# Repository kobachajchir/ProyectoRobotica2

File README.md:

> **Loader AFR2-20261028-05 / 0.9.0:** backup opcional leído del ATmega, aviso con No mostrar de nuevo y Preferencias; botón Flashear Firmware ATmega con menú Flashear último backup. [Ficha](AutoFinalRobo2-Contracts/changes/2026-10-28-05-loader-mega-backups.md) · [Plan de ambos métodos](AutoFinalRobo2-Contracts/hardware/PLAN_PRUEBA_FLASHER_MEGA.md). Fuente/documentación, sin compilar, ejecutar, validar, abrir COM ni flashear; atmega/esp/web sin nuevo firmware por05. Los avisos de versiones inferiores son históricos.

> **Loader AFR2-20261028-03 / 0.8.0:** selector **Método ESP** con instrucciones/casillas, instalar flasher en Mega y restaurar producto. [Plan A/B](AutoFinalRobo2-Contracts/hardware/PLAN_PRUEBA_FLASHER_MEGA.md), [ficha](AutoFinalRobo2-Contracts/changes/2026-10-28-03-loader-mega-flasher.md). Implementado en fuente; sin compilar, ejecutar, validar, abrir COM ni flashear en esta entrega.

> **Loader AFR2-20261027-19 / 0.3.0:** [monitor serie y errores](AutoFinalRobo2-Loader/MANUAL.html#monitor), selección de baudios, COM abrir/cerrar, captura de texto/bytes y avisos de reinicio, programación y verificación. [Ficha](AutoFinalRobo2-Contracts/changes/2026-10-27-19-loader-serial-monitor.md). Fuente/documentación; sin compilar/ejecutar/probar ni abrir COM/flashear.

> **Loader AFR2-20261027-16 / 0.2.0:** [MCP para conectar con Codex](AutoFinalRobo2-Loader/MCP.md), revisión de solicitudes en GUI, historial y refuerzos de interfaz. [Ficha](AutoFinalRobo2-Contracts/changes/2026-10-27-16-loader-mcp-ui.md). Fuente/documentación; sin compilar, ejecutar, registrar MCP, probar COM ni flashear en esta revisión.

> **Vigente AFR2-20261025-01:** [control directo7](AutoFinalRobo2-Contracts/contracts/DIRECT_CONTROL_7.md), sin permiso ni opciones de adquisición. Los tres módulos compilan con firmware0.9.0/Web0.2.0. Estado anterior inferior histórico.

> **Vigente AFR2-20261024-15:** [Matriz del maestro](AutoFinalRobo2-Contracts/docs/ALINEACION_MAESTRO.md):33comandos y59identidades OLED con fuentes complementarias. Calibración Web adquiere control al escribir; ESP/Web informan FS/paquete. Web/ESP compilados15; AVR sin nueva fuente, build12/EX01v6/firmware0.8.0/gates0. Sin brecha software definida identificada tras lectura; aceptación física, memoria dinámica, flash/SPI y planos CAD pendientes. Solo documentación en CAD, sin diseño nuevo. Estados inferiores históricos.

> **Fuente vigente AFR2-20261024-11:** encoder CLK/DT en D2/D3 por INT4/INT5, SW D42; cola y acciones en main. Hall PCINT2 A8–A15 con preferencia de captura por software, macro0. **Esta adaptación no está compilada ni probada**; build08 corresponde a la fuente anterior. ESP/Web conservan su estado10. [Ficha11](AutoFinalRobo2-Contracts/changes/2026-10-24-11-encoder-hall-interrupts.md). Los estados previos inferiores son históricos.

> Vigente **AFR2-20261024-04**: **modelo final incluido en ESP**, paquete **1.450.201 bytes gzip** (49,96% menos que los 2,90 MB iniciales). WebP, JS/CSS minificados y dependencias/componentes optimizados. Layout candidato: flash 4 MiB / LittleFS nominal 3 MiB, solicitado por el usuario; flash fisica sin identificar. Web full/esp y firmware ESP compilados; activos promovidos a data/dist. Sin navegador, imagen FS ni flasheo. Atmega y comandos conservan el estado de02. [Evidencia](AutoFinalRobo2-Contracts/changes/2026-10-24-04-final-model-littlefs.md). Los estados previos inferiores son historicos.

> Estado vigente **AFR2-20261024-02**, 24/10/2026: integración ROBO2/perfil2 + EX01v3 compilada en Atmega/ESP/Web; GOTO completo, configuración por catálogo compartido y jobs Wi-Fi OLED conectados. Paquete Web actualizado en ESP/data/dist. Sin pruebas de navegador/hardware ni flasheo; secuencias físicas mantienen bloqueo de memoria. Ver [matriz vigente](AutoFinalRobo2-Contracts/contracts/EX01_ALIGNMENT_3.md) y [evidencia](AutoFinalRobo2-Contracts/changes/2026-10-24-02-project-alignment.md). Los estados previos que siguen son históricos.

# AutoFinalRobo2

Un único repositorio Git local en D:/ProyectoRobotica2, organizado en seis módulos. [Informe maestro](INFORME_MAESTRO.md) · [Central documental](AutoFinalRobo2-Contracts/README.md) · [Git, exclusiones e historial](AutoFinalRobo2-Contracts/docs/ESTRUCTURA_Y_GIT.md).

| Módulo | Contenido |
| --- | --- |
| [Atmega](AutoFinalRobo2-Atmega/README.md) | C/avr-libc para ATmega2560; fuente parcial con endpoint/USART1 |
| [ESP](AutoFinalRobo2-ESP/README.md) | Arduino ESP8266/LittleFS; servidor y broker escritos, sin compilar |
| [Web](AutoFinalRobo2-Web/README.md) | React/Vite; paquete previo y cambios fuente pendientes de reconstruir |
| [Contracts](AutoFinalRobo2-Contracts/README.md) | Contratos, hardware, evidencia y cambios AFR2 |
| [CAD](AutoFinalRobo2-CAD/README.md) | KiCad, pieza nueva y modelo completo del auto; estructura e insumos |
| [Loader](AutoFinalRobo2-Loader/README.md) | Cargador Windows: compilación y flasheo guiados de ATmega/ESP/Web/LittleFS; fuente sin ejecutar ni probar |

El trabajo de diseño eléctrico y mecánico se concentra en AutoFinalRobo2-CAD. Los insumos que estaban en CADS se conservan allí con inventario; Documentacion/ conserva los documentos originales. No iniciar un Git dentro de cada módulo.

El .gitignore global excluye dependencias instaladas, cachés, compilados y exportaciones regenerables. Se conservan fuentes editables, manifests, lockfiles, bibliotecas propias e insumos únicos. Origin privado: [kobachajchir/ProyectoRobotica2](https://github.com/kobachajchir/ProyectoRobotica2), rama remota main. Los cuatro historiales anteriores y sus etiquetas están conservados en el Git global.

Leer AGENTS.md antes de trabajar. No ejecutar tests, compilaciones, validadores, ERC/DRC, flasheos ni pruebas físicas sin pedido expreso. El plan 3D distingue el ensamble base con inferencias documentadas de la pieza nueva/PCB pendientes de planos; aún no hay un modelo adaptado.

Registro: [AFR2-20261023-04](AutoFinalRobo2-Contracts/changes/2026-10-23-04-cad-and-monorepo.md).

## Plan 3D y continuación

[Plan completo de Fusion](AutoFinalRobo2-CAD/docs/PLAN_MODELO_3D_FUSION.md): ensamble del auto base sin cables, fuentes CAD y pendientes de la pieza nueva. MCP de Fusion existente. OLED 0,96 pulgadas y encoder KY-040 sin breakout/perilla como referencias para la integración futura. Registro [AFR2-20261023-05](AutoFinalRobo2-Contracts/changes/2026-10-23-05-fusion-plan-and-origin.md).

Para bajar el proyecto en la otra PC, con acceso a tu cuenta de GitHub:

```powershell
git clone https://github.com/kobachajchir/ProyectoRobotica2.git
```

Abrir la carpeta clonada y empezar por AutoFinalRobo2-CAD/docs/PLAN_MODELO_3D_FUSION.md. El clone usa main; los resguardos locales dentro de .git no se transfieren, pero los commits históricos y sus etiquetas sí.

## Firmware ESP y comunicación — AFR2-20261023-11

[Estado de implementación y pendientes](AutoFinalRobo2-Contracts/changes/2026-10-23-11-esp-server-and-mega-link.md): HTTP/WS/LittleFS/Wi-Fi ESP y endpoint USART1 AVR escritos; perfil binario AFR2 1 con sesión/transacción. Sin tests, compilación ni flasheo de esta entrega. Identificar flash/layout y completar servicios AVR; motores/lease/GOTO siguen pendientes. La Web fuente tiene ajustes de capacidades/STOP; paquete nuevo pendiente.

## AVR integrado y ROBO2 — AFR2-20261023-15

Atmega integra UART1/Timer0/TWI/I2C Manager/OLED/encoder en `src/main.c`, con
potencia inactiva y sensores desconocidos. Fuente sin compilar ni probar.
ROBO2/perfil 2 sustituye el framing UNER/perfil 1 en ambos extremos; mantiene
sesión/transacción y rutas por nibbles. Contrato vigente y evidencia en
AutoFinalRobo2-Contracts/changes/2026-10-23-15-robo2-atmega-ui.md. Para continuar
ESP: AutoFinalRobo2-ESP/docs/PROTOCOLO_ROBO2.md. Motores/lease/Hall/GOTO/UI remota
pendientes. No se ejecutaron builds, tests, validadores ni flasheos.

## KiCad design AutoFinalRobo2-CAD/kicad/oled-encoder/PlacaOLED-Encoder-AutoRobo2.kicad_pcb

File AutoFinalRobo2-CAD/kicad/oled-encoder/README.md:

# PCB OLED/encoder

Revisión final manual guardada en KiCad 10.99 mediante KiPilot MCP: PCB de 20×35×2 mm, componentes TH, pistas B.Cu y plano GND. Abrir `PlacaOLED-Encoder-AutoRobo2.kicad_pro`. R2/R3 de 10 kΩ a +3V3 para CLK/DT; JST power de 2 mm; encoder directo y OLED en socket de cuatro pines. [Entrega final, modelos y límites](../../docs/MODELO_FINAL_WEB_20261025.md). El informe A se conserva como historia.

Fuente de requisitos: [PCB OLED/encoder](../../../AutoFinalRobo2-Contracts/hardware/PCB_OLED_ENCODER.md). Usar bibliotecas propias de ../libraries y rutas relativas cuando se definan. Preservar fuentes; colocar Gerber, taladros, renders y otras salidas regenerables en ../../exports, fuera de Git.

Bibliotecas de proyecto definidas en `fp-lib-table` y `sym-lib-table`. Los modelos usan `${KIPRJMOD}/../libraries/3d/fusion-ui`; capacitores, biblioteca KiCad10. Los scripts en `scripts/` registran la construcción inicial, con protección para no sobrescribir una PCB ya poblada/ruteada. No reejecutar órdenes de ruteo sobre pistas existentes: dibujan nuevas pistas por MCP.

Exportar STEP con `kicad-cli pcb export step --user-origin 100x100mm --include-tracks --include-pads --include-zones --subst-models --output <exports/oled-encoder/PCB_UI_Final_20261025.step> <PCB>`. Se conserva la pose ajustada por el usuario en Fusion. No regenerar desde los parámetros iniciales: el archivo nativo contiene los ajustes finales. Esta exportación no ejecuta ERC/DRC.

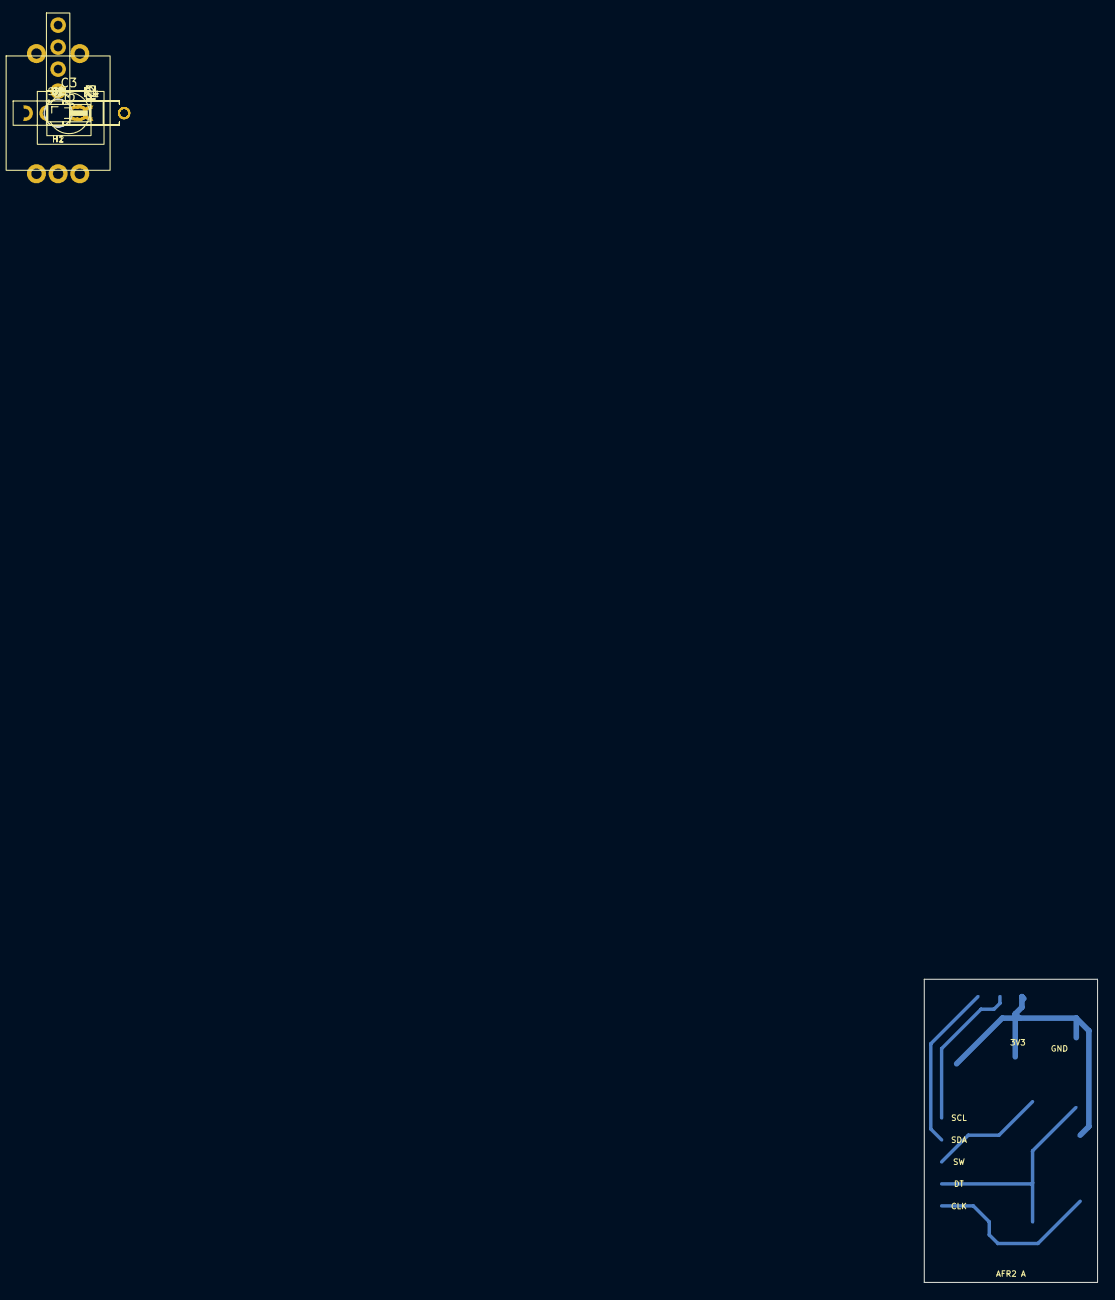
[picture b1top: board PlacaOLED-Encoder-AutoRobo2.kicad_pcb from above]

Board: 2 copper layers, 20.0 x 35.0 mm, 14 parts (0 on the bottom side), 8 nets.

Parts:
C1: 100nF 16V; C_Disc_2.5
C2: 4.7uF 10V; CP_D5_P2.5
C3: 104; CP_Radial_Tantal_D4.5mm_P2.50mm
H1, H2: MountingHole_3.2mm_M3
J1: DATOS CLK DT SW SDA SCL; Signals_Socket5
J2: 3V3 / GND; Power_1x02
J3: A5 Battery Sensor; PinHeader_1x01_P1.00mm_Horizontal
R1, R2, R3, R4: 10k; R_Axial_TH_7.62_Lift1.5
SW1: EC11 / KY040 sin breakout; Encoder_KY040_Bare
U1: OLED 0.96 128x64 / SOCKET 1x04; OLED096_Socket4

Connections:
+3V3: C1.1, C2.1, J2.1, R2.2, R3.2, U1.2 (VCC)
ENC_CLK: J1.1, R2.1, SW1.4 (DT)
ENC_DT: J1.2, R3.1, SW1.5 (CLK)
ENC_SW: J1.3, SW1.3 (SW)
GND: C1.2, C2.2, C3.2, J2.2, R4.2, SW1.1 (GND), SW1.2 (+), U1.1 (GND)
unnamed: C3.1, J3.1 (Pin_1_1), R1.2, R4.1
SCL: J1.5, U1.3 (SCL)
SDA: J1.4, U1.4 (SDA)
